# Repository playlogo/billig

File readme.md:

# Billig - A 3D printer from scratch

> *Designing a 3D printer from scratch in 5 days*

**Bom**: [Google sheets](https://docs.google.com/spreadsheets/d/1451xPwitG2cd0BywjLuyT1Flae_F1tCVU7JKSqZtRoc/edit?usp=sharing)  
**CAD**: [Onshape](https://cad.onshape.com/documents/d0a1f0aa5ccbfda89a60ed00/w/724bd13dc87be16ac72aafeb/e/c63896b50a2324a549602fe6?renderMode=0&uiState=67f44fca4d37325097df6c3a)

About the printer:

- 440x230x200mm printing volume
- 940x410x465mm frame
- Reuses a lot of parts from two "broken" [Anycubic Kobra 2 Neos](https://de.anycubic.com/products/kobra-2-neo)
- Direct drive extruder & dual 5020 part cooling
- Completely enclosed electronics
- Build-in ABL
- With a rpi zero & Klipper-Ready
- ~$500 (including the two broken printers)

Take a look at the [Journal (has lot's of pictures!)](JOURNAL.md), the [Design notes](notes.md) or the [custom PCB (that didn't make it)](pcb/readme.md)!

Note: The stls in `printer/stls/` are only for my reference, export & download the latest ones form Onshape!

## Roadmap

Use Elecrow 7.0" Esp32 Touch display as an interface for klipper.

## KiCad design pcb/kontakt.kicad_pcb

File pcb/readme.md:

# Kontakt - Fan & LED control board

|  | |
| ---------------------------------------|------------------------------------|
|  |  |

Features:

- 24V power input
- Build-in 5V 3A Stepdown (for RP2040 and external RPI)
- RP2040 with 128MB Flash
- 3 Port USB hub
- 1x UART connection
- 1x ARGB connection
- 2x High current 24V PWM outputs (5A)
- 4x Low current 24V PWM outputs (2A)
- [A 3D printable case](case/) with an included 30mm fan, can be mounted to a DIN rail with [this adapter](https://www.printables.com/model/259120-horizontal-ssr-din-rail-mount/files)

Why ?: I originally only wanted to slap a rpi pico onto a pcb and add 6 mosfets to it, but like you can see I got sidetracked and added my own rp2040 (my first one!), a step-down converter (also a first) and a USB hub...

It'll be used to control the fans inside the electronics enclosure and connect the 2 control boards to the one usb port of the RPI Zero 2w, which it will also power. The high current PWM outputs are for eventual LED bar upgrades, which might or might not happen.

Firmware: I'll be using Klipper on the RP2040 with [this extension module](https://github.com/julianschill/klipper-led_effect) to control the Neopixel

Schematic: [Here](../files/schematic.pdf)

Libraries:

- [easyeda2kicad](https://github.com/uPesy/easyeda2kicad.py), needs to be installed separately, used for downloading LCSC schematics & footprints
  - Run `easyeda2kicad --full --lcsc_id=<id>` to download each component (one-by-one, yes...)

## Components

LCSC IDs:

- C2040 - RP2040
- C26537 - LDO
- C778164 - 2x Button
- C113767 - SPI Flash
- C20625731 - Crystal
- C7429053 - High current mosfet
- C5364313 - Low current mosfet
- C10002 - LM2596 3A Step down - [datasheet](https://www.lcsc.com/datasheet/lcsc_datasheet_2410010301_Texas-Instruments-LM2596SX-5-0-NOPB_C10002.pdf)
  - L1: 47uH L39 - C7529419
  - Cout: 330uF/35V - C242140
  - D1: C7503125
  - Cin: 680uF/35V - C178718
- C2915639 - Screw terminal
- C2988369 - USB C Female connector
- C192893 - USB Hub chip
- C503996 - USB Female plug

Resistors & Capacitors

- 10K C5140188
- 5.1k C26023
- 1k C17513
- 27.4ohm C2079437

- 100nF C29926
- 1uF C541528
- 10uF C1713
- 15pF C5186731

## BOM

### Parts

> Note: This is my first time soldering a rp2040 (QFN-* package in general) :D

| LCSC ID   | Name                          | Amount      |
|-----------|-------------------------------|-------------|
| C2040     | RP2040                        | 1x          |
| C26537    | LDO                           | MOQ (5)     |
| C778164   | 2x Button                     | MOQ (5)     |
| C113767   | SPI Flash                     | 1x          |
| C20625731 | Crystal                       | 1x          |
| C7429053  | High current mosfet           | 2x          |
| C5364313  | Low current mosfet            | MOQ(10)     |
| C10002    | LM2596 3A Step down           | 1x          |
| C7529419  | LM2596 3A Step down (L1)      | 1x          |
| C242140   | LM2596 3A Step down (Cout)    | MOQ (5)     |
| C7503125  | LM2596 3A Step down (D1)      | MOQ (5)     |
| C178718   | LM2596 3A Step down (Cin)     | 1x          |
| C2915639  | Screw terminal                | MOQ (5)     |
| C2988369  | USB C Female connector        | MOQ (5)     |
| C192893   | USB Hub chip                  | MOQ (5)     |
| C503996   | USB Female plug               | MOQ (10)    |
| C5140188  | 10K                           | MOQ (100)   |
| C26023    | 5.1k                          | MOQ (100)   |
| C17513    | 1k                            | MOQ (100)   |
| C2079437  | 27.4ohm                       | MOQ(50)     |  
| C29926    | 100nF                         | MOQ(50)     |
| C541528   | 1uF                           | MOQ(50)     |
| C1713     | 10uF                          | MOQ(20)     |
| C5186731  | 15pF                          | MOQ(100)    |

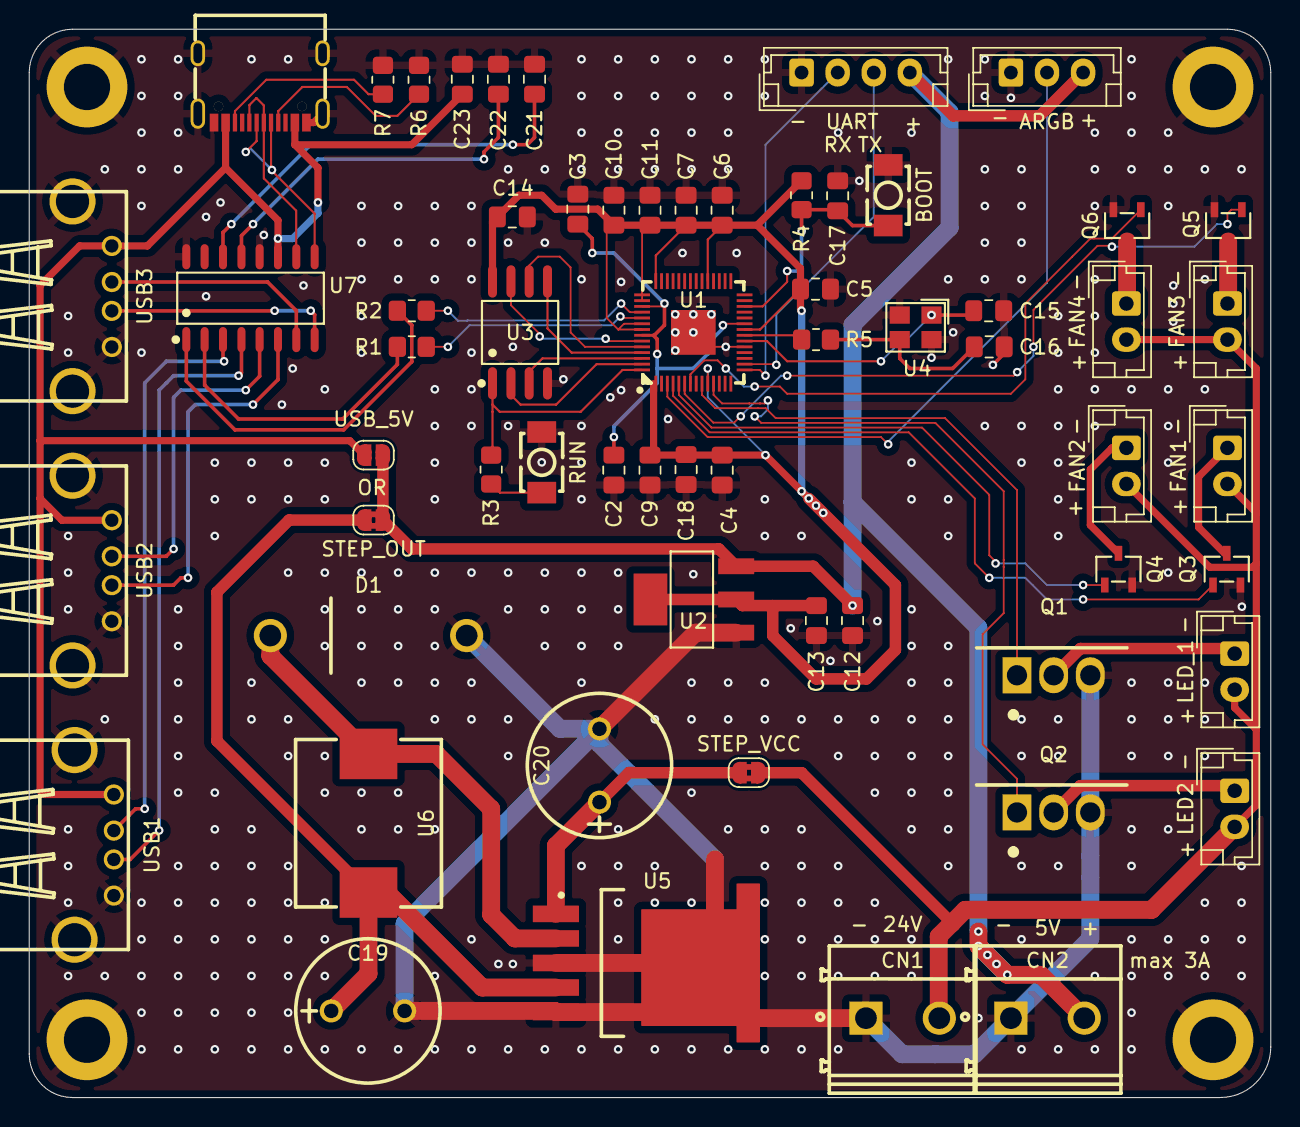
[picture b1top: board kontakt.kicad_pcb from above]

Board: 2 copper layers, 86.0 x 74.0 mm, 65 parts (0 on the bottom side), 51 nets.

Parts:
C2, C4, C5, C6, C7, C9, C10, C14, C17: 100n; C_0805_2012Metric_Pad1.18x1.45mm_HandSolder
C3, C11: 1u; C_0805_2012Metric_Pad1.18x1.45mm_HandSolder
C12, C13, C18: 10u; C_0805_2012Metric_Pad1.18x1.45mm_HandSolder
C15, C16: 15p; C_0805_2012Metric_Pad1.18x1.45mm_HandSolder
C19: EEUEB1V331B; CAP-TH_BD10.0-P5.00-D1.0-FD
C20: EEUFR1V681; CAP-TH_BD10.0-P5.00-D1.0-FD
C21, C22, C23: 10uF; C_0805_2012Metric_Pad1.18x1.45mm_HandSolder
CN1: Vin; CONN-TH_2P-P5.08_DIBO_DB128V-5.08
CN2: 5V; CONN-TH_2P-P5.08_DIBO_DB128V-5.08
D1: 1N5824_C7503125; DO-27_BD5.3-L8.4-P12.40-D1.3-RD
H1, H2, H3, H4: MountingHole_Pad; MountingHole_3.2mm_M3_DIN965_Pad
J1: UART; JST_EH_B4B-EH-A_1x04_P2.50mm_Vertical
J2: LED_1; JST_EH_B2B-EH-A_1x02_P2.50mm_Vertical
J3: LED2; JST_EH_B2B-EH-A_1x02_P2.50mm_Vertical
J4: FAN1; JST_EH_B2B-EH-A_1x02_P2.50mm_Vertical
J5: ARGB; JST_EH_B3B-EH-A_1x03_P2.50mm_Vertical
J6: FAN2; JST_EH_B2B-EH-A_1x02_P2.50mm_Vertical
J7: FAN3; JST_EH_B2B-EH-A_1x02_P2.50mm_Vertical
J8: FAN4; JST_EH_B2B-EH-A_1x02_P2.50mm_Vertical
JP1: STEP_VCC; SolderJumper-2_P1.3mm_Bridged2Bar_RoundedPad1.0x1.5mm
JP2: STEP_OUT; SolderJumper-2_P1.3mm_Bridged2Bar_RoundedPad1.0x1.5mm
JP3: USB_5V; SolderJumper-2_P1.3mm_Open_RoundedPad1.0x1.5mm
Q1, Q2: IRLB8721PBF-VB; TO-220AB-3_L10.4-W4.6-P2.54-L
Q3, Q4, Q5, Q6: IRLML6344; SOT-23-3_L3.0-W1.7-P0.95-LS2.9-BR
R1, R2: 27.4; R_0805_2012Metric_Pad1.20x1.40mm_HandSolder
R3, R5: 1k; R_0805_2012Metric_Pad1.20x1.40mm_HandSolder
R4: 10k; R_0805_2012Metric_Pad1.20x1.40mm_HandSolder
R6, R7: 5.1k; R_0805_2012Metric_Pad1.20x1.40mm_HandSolder
SW1, SW2: GT-TC029A-H020-L1N; SW-SMD_L3.9-W2.9-LS5.0
U1: RP2040; LQFN-56_L7.0-W7.0-P0.4-EP
U2: NCP1117ST33T3G; SOT-223-3_L6.5-W3.4-P2.30-LS7.0-BR
U3: W25Q128JVSIQ; SOIC-8_L5.3-W5.3-P1.27-LS8.0-BL
U4: ABM8-272-T3_C20625731; CRYSTAL-SMD_4P-L3.2-W2.5-BL
U5: LM2596SX-5.0/NOPB; TO-263-5_L10.2-W8.9-P1.70-TL
U6: CYA1050-47UH; IND-SMD_L11.6-W10.1
U7: SL2.1A; SOP-16_L10.0-W3.9-P1.27-LS6.0-BL
U8: GT-USB-7010ASV; USB-C-SMD_G-SWITCH_GT-USB-7010ASV
USB1, USB2, USB3: KH-AF90DIP-112; USB-A-TH_USB-A-F-90

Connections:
+1V1: C2.1, C3.1, U1.23 (DVDD), U1.45 (VREG_VOUT), U1.50 (DVDD)
+3.3V: C4.1, C5.1, C6.1, C7.1, C9.1, C10.1, C11.1, C13.1, C14.1, C18.1, R4.2, U1.1 (IOVDD), U1.10 (IOVDD), U1.22 (IOVDD), U1.33 (IOVDD), U1.42 (IOVDD), U1.43 (ADC_AVDD), U1.44 (VREG_IN), U1.48 (USB_VDD), U1.49 (IOVDD), U2.2 (OUTPUT), U2.4 (TAB), U3.8 (VCC)
+5V: C12.1, CN2.2, J1.4, J5.3, JP2.2 (B), JP3.2 (B), U2.3 (INPUT)
/Peripherals/ARGB: J5.2, U1.3 (GPIO1)
/Peripherals/FAN_1: Q3.1 (G), U1.4 (GPIO2)
/Peripherals/FAN_2: Q4.1 (G), U1.5 (GPIO3)
/Peripherals/FAN_3: Q5.1 (G), U1.6 (GPIO4)
/Peripherals/FAN_4: Q6.1 (G), U1.7 (GPIO5)
/Peripherals/LED_1: Q1.1 (G), U1.9 (GPIO7)
/Peripherals/LED_2: Q2.1 (G), U1.11 (GPIO8)
/Peripherals/UART_RX: J1.2, U1.15 (GPIO12)
/Peripherals/UART_TX: J1.3, U1.16 (GPIO13)
/rpi/QSPI_SCLK: U1.52 (QSPI_SCLK), U3.6 (CLK)
/rpi/QSPI_SD0: U1.53 (QSPI_SD0), U3.5 (DI(IO0))
/rpi/QSPI_SD1: U1.55 (QSPI_SD1), U3.2 (DO(IO1))
/rpi/QSPI_SD2: U1.54 (QSPI_SD2), U3.3 (WP#(IO2))
/rpi/QSPI_SD3: U1.51 (QSPI_SD3), U3.7 (HOLD#orRESET#(IO3))
/rpi/QSPI_SS: R3.1, U1.56 (QSPI_SS), U3.1 (~CS)
/rpi/RUN: C17.1, R4.1, SW2.1, U1.26 (RUN)
/rpi/USB_D+: R1.2, U7.2 (DP4)
/rpi/USB_D-: R2.2, U7.1 (DM4)
/rpi/XIN: C15.2, U1.20 (XIN), U4.1
/rpi/XOUT: R5.2, U1.21 (XOUT)
/usb/D+: U7.10 (DP), U8.A6 (DP1), U8.B6 (DP2)
/usb/D-: U7.9 (DM), U8.A7 (DN1), U8.B7 (DN2)
GND: C2.2, C3.2, C4.2, C5.2, C6.2, C7.2, C9.2, C10.2, C11.2, C12.2, C13.2, C14.2, C15.1, C16.1, C17.2, C18.2, C19.2, C20.2, C21.1, C22.1, C23.2, CN1.1, CN2.1, D1.2 (A), H1.1, H2.1, H3.1, H4.1, J1.1, J5.1, Q1.3 (S), Q2.3 (S), Q3.2 (S), Q4.2 (S), Q5.2 (S), Q6.2 (S), R6.2, R7.2, SW1.2, SW2.2, U1.19 (TESTEN), U1.57 (GND), U2.1 (ADJ/GND), U3.4 (GND), U4.2 (GND), U4.4 (GND), U5.3 (GND), U5.5 (~ON/OFF), U5.6 (GND), U7.12 (GND), U7.16 (XIN), U8.1 (SHELL), U8.2 (SHELL), U8.3 (SHELL), U8.4 (SHELL), U8.A1B12 (GND), U8.B1A12 (GND), USB1.0, USB1.4 (GND), USB2.0, USB2.4 (GND), USB3.0, USB3.4 (GND)
unnamed: C16.2, R5.1, U4.3
unnamed: D1.1 (K), U5.2 (OUTPUT), U6.1
unnamed: J2.1, Q1.2 (D)
unnamed: J3.1, Q2.2 (D)
unnamed: J4.1, Q3.3 (D)
unnamed: J6.1, Q4.3 (D)
unnamed: J7.1, Q5.3 (D)
unnamed: J8.1, Q6.3 (D)
unnamed: C20.1, JP1.1 (A), U5.1 (VIN)
unnamed: C19.1, JP2.1 (A), U5.4 (FB), U6.2
unnamed: R3.2, SW1.1
unnamed: R2.1, U1.46 (USB_DM)
unnamed: R1.1, U1.47 (USB_DP)
unnamed: U7.7 (DM1), USB3.2 (D-)
unnamed: U7.5 (DM2), USB2.2 (D-)
unnamed: U7.3 (DM3), USB1.2 (D-)
unnamed: U7.8 (DP1), USB3.3 (D+)
unnamed: U7.6 (DP2), USB2.3 (D+)
unnamed: U7.4 (DP3), USB1.3 (D+)
unnamed: C21.2, U7.14 (VDD18)
unnamed: C22.2, U7.13 (VDD33)
unnamed: R6.1, U8.A5 (CC1)
unnamed: R7.1, U8.B5 (CC2)
VBUS: C23.1, JP3.1 (A), U7.11 (VDD5), U8.A4B9 (VBUS), U8.B4A9 (VBUS), USB1.1 (VCC), USB2.1 (VCC), USB3.1 (VCC)
VCC: CN1.2, J2.2, J3.2, J4.2, J6.2, J7.2, J8.2, JP1.2 (B)

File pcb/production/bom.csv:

Designator,Footprint,Quantity,Value,LCSC Part #
"C10, C14, C17, C2, C4, C5, C6, C7, C9",0805,9,100n,
"C11, C3",0805,2,1u,
"C12, C13, C18",0805,3,10u,
"C15, C16",0805,2,15p,
C19,CAP-TH_BD10.0-P5.00-D1.0-FD,1,EEUEB1V331B,C242140
C20,CAP-TH_BD10.0-P5.00-D1.0-FD,1,EEUFR1V681,C178718
"C21, C22, C23",0805,3,10uF,
CN1,CONN-TH_2P-P5.08_DIBO_DB128V-5.08,1,Vin,C2915639
CN2,CONN-TH_2P-P5.08_DIBO_DB128V-5.08,1,5V,C2915639
D1,DO-27_BD5.3-L8.4-P12.40-D1.3-RD,1,1N5824_C7503125,C7503125
J1,JST_EH_B4B-EH-A_1x04_P2.50mm_Vertical,1,UART,
J2,JST_EH_B2B-EH-A_1x02_P2.50mm_Vertical,1,LED_1,
J3,JST_EH_B2B-EH-A_1x02_P2.50mm_Vertical,1,LED2,
J4,JST_EH_B2B-EH-A_1x02_P2.50mm_Vertical,1,FAN1,
J5,JST_EH_B3B-EH-A_1x03_P2.50mm_Vertical,1,ARGB,
J6,JST_EH_B2B-EH-A_1x02_P2.50mm_Vertical,1,FAN2,
J7,JST_EH_B2B-EH-A_1x02_P2.50mm_Vertical,1,FAN3,
J8,JST_EH_B2B-EH-A_1x02_P2.50mm_Vertical,1,FAN4,
"Q1, Q2",TO-220AB-3_L10.4-W4.6-P2.54-L,2,IRLB8721PBF-VB,C7429053
"Q3, Q4, Q5, Q6",SOT-23-3_L3.0-W1.7-P0.95-LS2.9-BR,4,IRLML6344,C5364313
"R1, R2",0805,2,27.4,
"R3, R5",0805,2,1k,
R4,0805,1,10k,
"R6, R7",0805,2,5.1k,
"SW1, SW2",SW-SMD_L3.9-W2.9-LS5.0,2,GT-TC029A-H020-L1N,C778164
U1,LQFN-56_L7.0-W7.0-P0.4-EP,1,RP2040,C2040
U2,SOT-223-3_L6.5-W3.4-P2.30-LS7.0-BR,1,NCP1117ST33T3G,C26537
U3,SOIC-8_L5.3-W5.3-P1.27-LS8.0-BL,1,W25Q128JVSIQ,C113767
U4,CRYSTAL-SMD_4P-L3.2-W2.5-BL,1,ABM8-272-T3_C20625731,C20625731
U5,TO-263-5_L10.2-W8.9-P1.70-TL,1,LM2596SX-5.0/NOPB,C10002
U6,IND-SMD_L11.6-W10.1,1,CYA1050-47UH,C7529419
U7,SOP-16_L10.0-W3.9-P1.27-LS6.0-BL,1,SL2.1A,C192893
U8,USB-C-SMD_G-SWITCH_GT-USB-7010ASV,1,GT-USB-7010ASV,C2988369
"USB1, USB2, USB3",USB-A-TH_USB-A-F-90,3,KH-AF90DIP-112,C503996

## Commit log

2025-03-09 Improved docs
2025-03-09 minor improvements
2025-04-07 started working on docs
2025-04-07 pushhh
2025-04-07 pushhhh
2025-04-07 push
2025-04-08 Improved docs, updated bom
2025-04-08 Improved docs!
2025-04-08 once again, improved docs
2025-04-09 Added pcb!
2025-04-10 Improved PCB docs
2025-05-09 Create LICENSE
2025-07-17 Updated journal for finished printer
2025-07-17 Minor fixes
2025-07-17 Journal fixes
2025-07-19 Fixed image links in pcb readme
2026-01-14 Improved Kontakt PCB
2026-01-14 Improved readme
2026-01-14 Improvements
2026-01-25 Added case for pcb
